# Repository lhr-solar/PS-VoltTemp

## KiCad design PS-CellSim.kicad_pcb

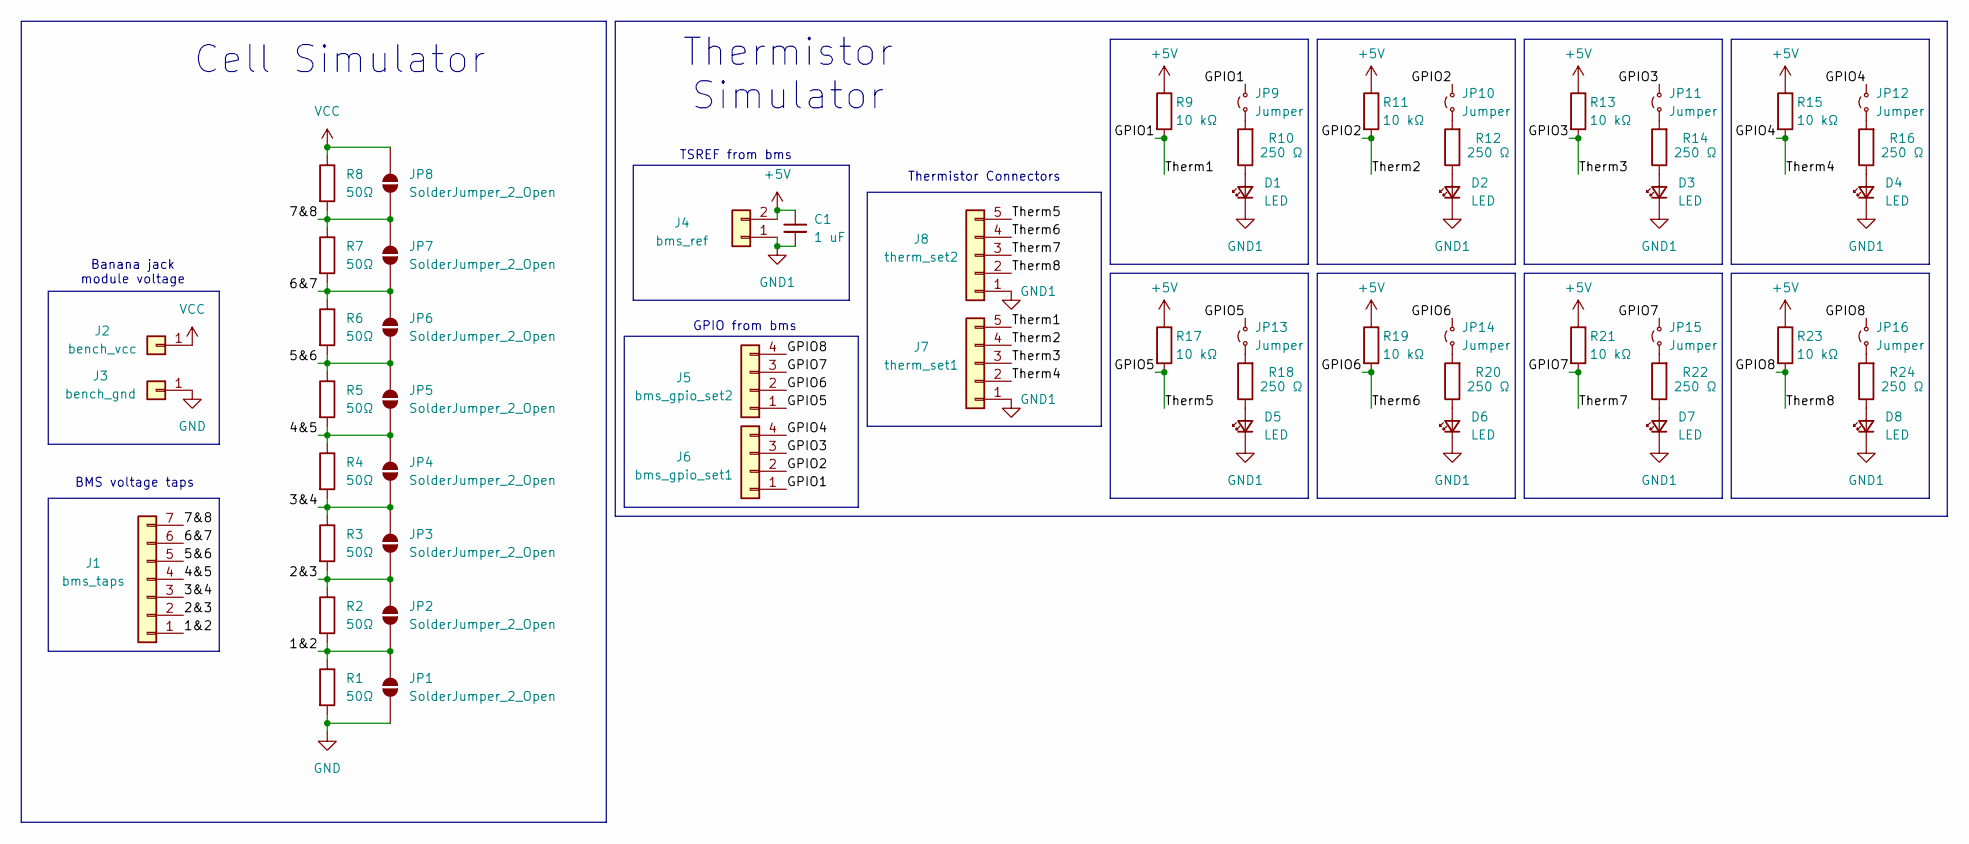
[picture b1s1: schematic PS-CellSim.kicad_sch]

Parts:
C1: 1 uF; C_0603_1608Metric
D1, D2, D3, D4, D5, D6, D7, D8: LED; LED_0603_1608Metric
J1: bms_taps; Molex_Nano-Fit_105313-xx07_1x07_P2.50mm_Horizontal
J2: bench_vcc; Banana_Jack_1_Pin_4mm
J3: bench_gnd; Banana_Jack_1_Pin_4mm
J4: bms_ref; Molex_Nano-Fit_105313-xx02_1x02_P2.50mm_Horizontal
J5: bms_gpio_set2; Molex_Nano-Fit_105313-xx04_1x04_P2.50mm_Horizontal
J6: bms_gpio_set1; Molex_Nano-Fit_105313-xx04_1x04_P2.50mm_Horizontal
J7: therm_set1; Molex_Nano-Fit_105313-xx05_1x05_P2.50mm_Horizontal
J8: therm_set2; Molex_Nano-Fit_105313-xx05_1x05_P2.50mm_Horizontal
JP1, JP2, JP3, JP4, JP5, JP6, JP7, JP8: SolderJumper_2_Open; SolderJumper-2_P1.3mm_Open_TrianglePad1.0x1.5mm
JP9, JP10, JP11, JP12, JP13, JP14, JP15, JP16: Jumper; PinHeader_1x02_P2.00mm_Vertical
R1, R2, R3, R4, R5, R6, R7, R8: 50Ω; R_0603_1608Metric
R9, R11, R13, R15, R17, R19, R21, R23: 10 kΩ; R_0603_1608Metric
R10, R12, R14, R16, R18, R20, R22, R24: 250 Ω; R_0603_1608Metric

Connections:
+5V: C1.1, J4.2, R9.1, R11.1, R13.1, R15.1, R17.1, R19.1, R21.1, R23.1
/1&2: J1.1, JP1.2 (B), JP2.1 (A), R1.1, R2.2
/2&3: J1.2, JP2.2 (B), JP3.1 (A), R2.1, R3.2
/3&4: J1.3, JP3.2 (B), JP4.1 (A), R3.1, R4.2
/4&5: J1.4, JP4.2 (B), JP5.1 (A), R4.1, R5.2
/5&6: J1.5, JP5.2 (B), JP6.1 (A), R5.1, R6.2
/6&7: J1.6, JP6.2 (B), JP7.1 (A), R6.1, R7.2
/7&8: J1.7, JP7.2 (B), JP8.1 (A), R7.1, R8.2
/GPIO1: J6.1, J7.5, JP9.2 (B), R9.2
/GPIO2: J6.2, J7.4, JP10.2 (B), R11.2
/GPIO3: J6.3, J7.3, JP11.2 (B), R13.2
/GPIO4: J6.4, J7.2, JP12.2 (B), R15.2
/GPIO5: J5.1, J8.5, JP13.2 (B), R17.2
/GPIO6: J5.2, J8.4, JP14.2 (B), R19.2
/GPIO7: J5.3, J8.3, JP15.2 (B), R21.2
/GPIO8: J5.4, J8.2, JP16.2 (B), R23.2
GND: J3.1 (Pin_1_1), JP1.1 (A), R1.2
GND1: C1.2, D1.1 (K), D2.1 (K), D3.1 (K), D4.1 (K), D5.1 (K), D6.1 (K), D7.1 (K), D8.1 (K), J4.1, J7.1, J8.1
unnamed: D1.2 (A), R10.1
unnamed: D2.2 (A), R12.1
unnamed: D3.2 (A), R14.1
unnamed: D4.2 (A), R16.1
unnamed: D5.2 (A), R18.1
unnamed: D6.2 (A), R20.1
unnamed: D7.2 (A), R22.1
unnamed: D8.2 (A), R24.1
unnamed: JP9.1 (A), R10.2
unnamed: JP10.1 (A), R12.2
unnamed: JP11.1 (A), R14.2
unnamed: JP12.1 (A), R16.2
unnamed: JP13.1 (A), R18.2
unnamed: JP14.1 (A), R20.2
unnamed: JP15.1 (A), R22.2
unnamed: JP16.1 (A), R24.2
VCC: J2.1 (Pin_1_1), JP8.2 (B), R8.1

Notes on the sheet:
Cell Simulator
BMS voltage taps
Banana jack module voltage
TSREF from bms
Thermistor Connectors
GPIO from bms
Thermistor Simulator

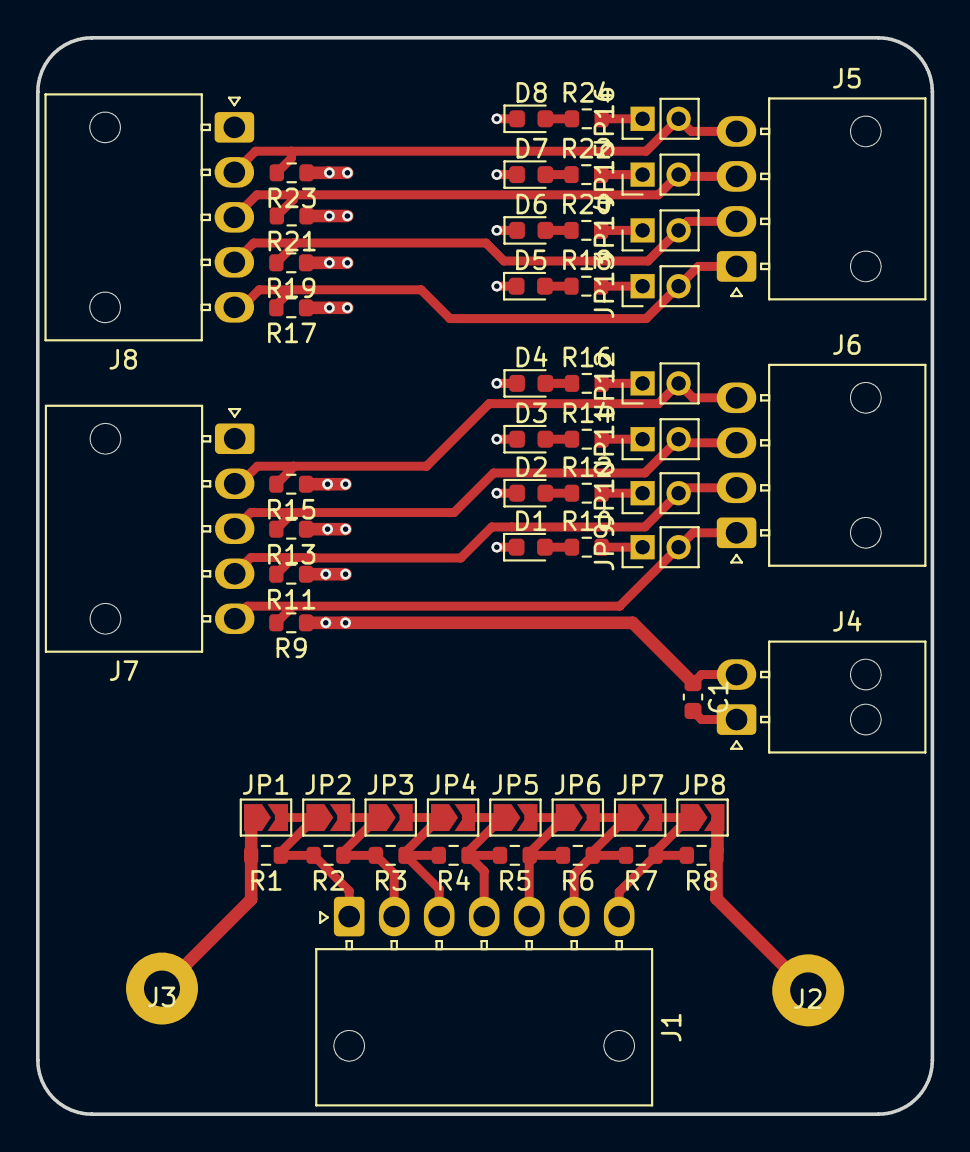
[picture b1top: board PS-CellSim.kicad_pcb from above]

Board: 2 copper layers, 49.7 x 59.8 mm, 57 parts (0 on the bottom side), 35 nets.

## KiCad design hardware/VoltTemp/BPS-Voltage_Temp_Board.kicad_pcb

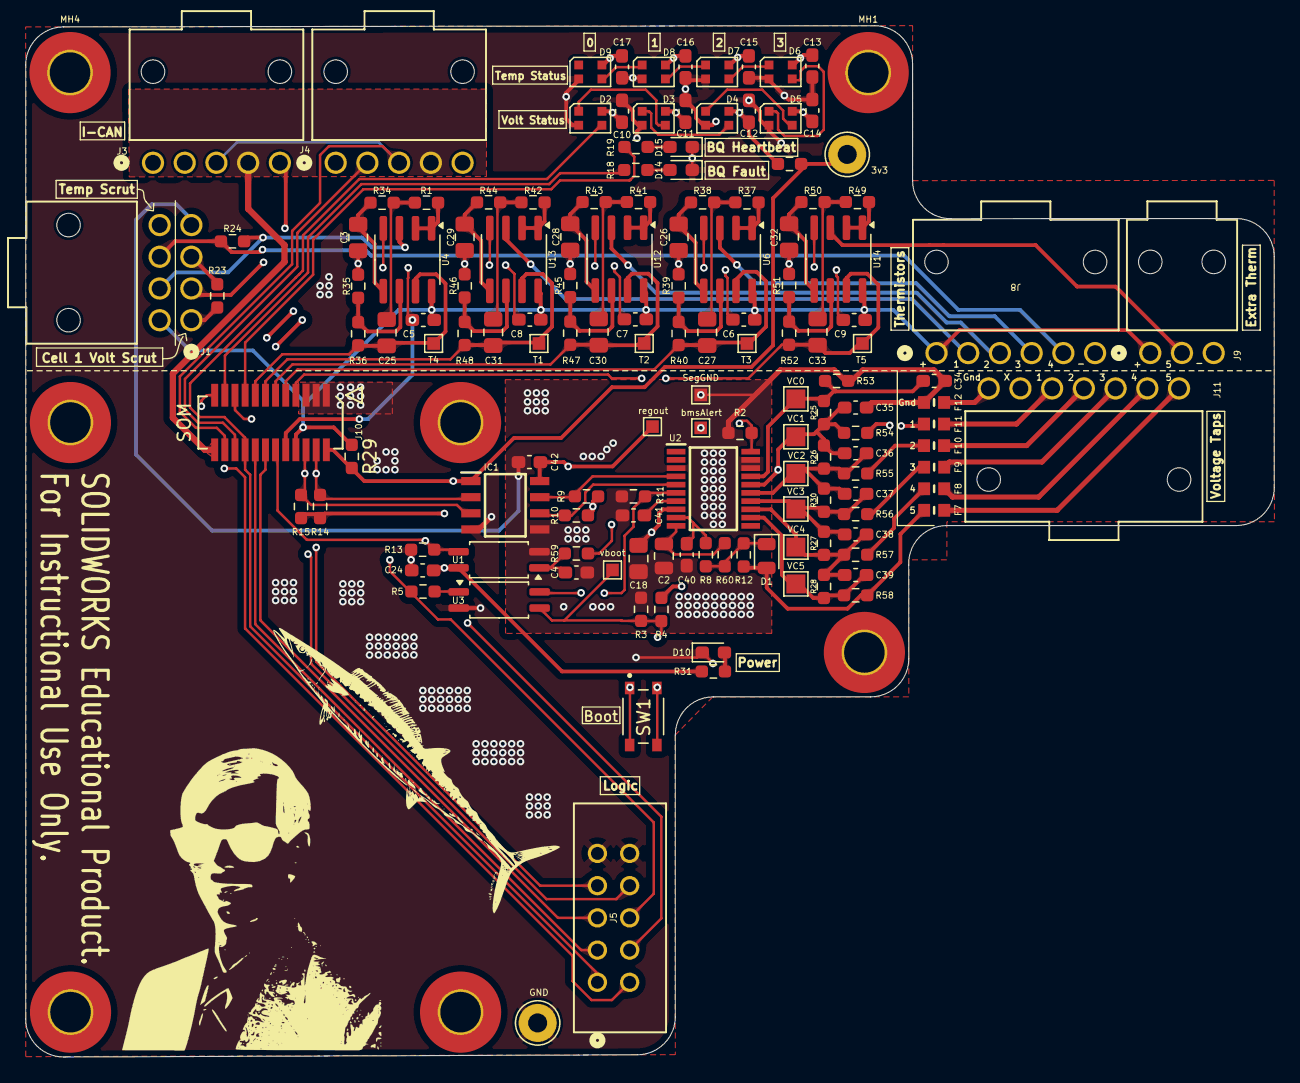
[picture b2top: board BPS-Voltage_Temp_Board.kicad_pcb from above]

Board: 4 copper layers, 98.4 x 81.3 mm, 146 parts (0 on the bottom side), 91 nets.

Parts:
C2: 10μF; C_0805_2012Metric
C3, C26, C28, C29, C32: 1uF; C_0805_2012Metric_Pad1.18x1.45mm_HandSolder
C4: 470pF; C_0603_1608Metric_Pad1.08x0.95mm_HandSolder
C5, C6, C7, C8, C9, C24, C42: 0.1uF; C_0603_1608Metric_Pad1.08x0.95mm_HandSolder
C10, C11, C12, C13, C14, C15, C16, C17: 100nF; C_0603_1608Metric_Pad1.08x0.95mm_HandSolder
C18: 4.7uF; C_0805_2012Metric_Pad1.18x1.45mm_HandSolder
C25, C27, C30, C31, C33: 1.2uF; C_0805_2012Metric_Pad1.18x1.45mm_HandSolder
C34, C35, C36, C37, C38, C39, C40, C41: 1uF; C_0603_1608Metric_Pad1.08x0.95mm_HandSolder
D1: D_Zener_Small; D_0805_2012Metric
D2, D3, D4, D5, D6, D7, D8, D9: WS2812B-2020; LED_WS2812B-2020_PLCC4_2.0x2.0mm
D10: 3v3; LED_0603_1608Metric_Pad1.05x0.95mm_HandSolder
D14: BQ-Fault; LED_0603_1608Metric_Pad1.05x0.95mm_HandSolder
D15: BQ_HB; LED_0603_1608Metric_Pad1.05x0.95mm_HandSolder
F7, F8, F9, F10, F11: 10mA; ptc_fuse_FUSC1607X75N
F12: 40mA; ptc_fuse_FUSC1607X75N
IC1: ISO1641BDR
J1: ScrutineeringConn; nanofit_02x04
J3, J4: Conn_01x05; nanofit_01x05
J5: Logic_Analyzer; CONN_SFH11-xxxC-D05-ST-XX_SUL
J8: Conn_01x06; 1053131106
J9: Conn_01x03; 1053131103
J10: 53307-2471; PeripheralSOM
J11: Conn_01x07; 1053131107
LOGO1: Dr. Hallock; Hallock_Image_Small
LOGO2: LHRs; LHRs_LOGO
MH1, MH3, MH4: MountingHole_Pad; MountingHole_3.2mm_M3_Pad_TopBottom
R1, R37, R41, R42, R49: 8.2kΩ; R_0603_1608Metric_Pad0.98x0.95mm_HandSolder
R2: 510kΩ; R_0603_1608Metric_Pad0.98x0.95mm_HandSolder
R3, R5: 2kΩ; R_0603_1608Metric_Pad0.98x0.95mm_HandSolder
R4, R9, R10, R11, R13, R14, R15: 10kΩ; R_0603_1608Metric_Pad0.98x0.95mm_HandSolder
R6, R23, R24, R25, R26, R27, R28, R29, R30: 0Ω; R_0603_1608Metric_Pad0.98x0.95mm_HandSolder
R8, R12: 1kΩ; R_0603_1608Metric_Pad0.98x0.95mm_HandSolder
R18, R19: 120; R_0603_1608Metric_Pad0.98x0.95mm_HandSolder
R31: 4.3k; R_0603_1608Metric_Pad0.98x0.95mm_HandSolder
R34, R38, R43, R44, R50: 27kΩ; R_0603_1608Metric_Pad0.98x0.95mm_HandSolder
R35, R36, R39, R40, R45, R46, R47, R48, R51, R52: 2.7kΩ; R_0603_1608Metric_Pad0.98x0.95mm_HandSolder
R53, R54, R55, R56, R57, R58, R59, R60: 100Ω; R_0603_1608Metric_Pad0.98x0.95mm_HandSolder
SW1: BOOT; SW_TL3365AF180QG
TP1: Regout; TestPoint_Pad_1.0x1.0mm
TP2, TP5: TestPoint; TestPoint_THTPad_D3.0mm_Drill1.5mm
TP3: bmsAlert; TestPoint_Pad_1.0x1.0mm
TP4: SegGND; TestPoint_Pad_1.0x1.0mm
TP6: VBoot; TestPoint_Pad_1.0x1.0mm
TP11, TP12, TP13, TP14, TP15: TP_TempOut; TestPoint_Pad_1.0x1.0mm
U1, U3: EL3H7
U2: BQ7692003PW
U4, U6, U12, U13, U14: TLV9062xD; SOIC-8_3.9x4.9mm_P1.27mm
VC0, VC1, VC2, VC3, VC4, VC5: TestPoint; TestPoint_Pad_1.5x1.5mm

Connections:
+3.3V: C24.1, IC1.1 (VCC1), J10.2 (+3.3v), R6.1, R14.2, R15.2, R29.2, R31.1, TP2.1, U1.4
+24V: J3.4, J4.4, J10.24 (+24V_In)
/BQ_Fault: J10.21 (SPI1_MISO), R18.1
/BQ_HB: J10.17 (SPI1_MOSI), R19.1
/FaultIndicators/ws2812b_pwr: C10.1, C11.1, C12.1, C13.1, C14.1, C15.1, C16.1, C17.1, D2.4 (VDD), D3.4 (VDD), D4.4 (VDD), D5.4 (VDD), D6.4 (VDD), D7.4 (VDD), D8.4 (VDD), D9.4 (VDD), R6.2
/I-CAN_H: J3.3, J4.3, J10.22 (CAN_H)
/I-CAN_L: J3.2, J4.2, J10.20 (CAN_L)
/LedDin: D2.3 (DIN), J5.1 (CH0), J10.18 (SPI2_SCK)
/PB3: J5.2 (CH1), J10.23 (SPI1_SCK)
/PB14: J5.5 (CH4), J10.14 (SPI2_MISO)
/PB15: J5.3 (CH2), J10.16 (SPI2_MOSI)
/ScrutineeringConn/1&2COM: F11.2, J1.3, R23.1
/ScrutineeringConn/1&2COM_OUT: J1.1, R23.2, R54.2
/ScrutineeringConn/rawTemperature4_Pre: J1.7, J8.5, R24.1
/ShieldGND: J1.2, J3.5, J4.5
/TemperatureConn/rawTemperature1: J8.2, U13.3 (+)
/TemperatureConn/rawTemperature2: J8.3, U12.3 (+)
/TemperatureConn/rawTemperature3: J8.4, U6.3 (+)
/TemperatureConn/rawTemperature4: J1.6, R24.2, U4.3 (+)
/TemperatureConn/rawTemperature5: J9.2, U14.3 (+)
/TemperatureFilters/Temperature1: C31.2, J10.13 (ADC1_IN10), R48.2, TP14.1, U13.7
/TemperatureFilters/Temperature2: C30.2, J10.11 (ADC1_IN9), R47.2, TP13.1, U12.7
/TemperatureFilters/Temperature3: C27.2, J10.9 (ADC1_IN7), R40.2, TP12.1, U6.7
/TemperatureFilters/Temperature4: C25.2, J10.15 (ADC1_IN11), R36.2, TP11.1, U4.7
/TemperatureFilters/Temperature5: C33.2, J10.7 (OPAMP1_VINP), R52.2, TP15.1, U14.7
/VoltageConn/1&2COM_ext: F11.1, J11.5
/VoltageConn/2&3COM: F10.2, R55.2
/VoltageConn/2&3COM_ext: F10.1, J11.4
/VoltageConn/3&4COM: F9.2, R56.2
/VoltageConn/3&4COM_ext: F9.1, J11.3
/VoltageConn/4&5COM: F8.2, R57.2
/VoltageConn/4&5COM_ext: F8.1, J11.2
/VoltageConn/VC0: C34.2, R25.2, R53.1, U2.17 (VC0), VC0.1
/VoltageConn/VC1: C35.1, C36.2, R4.1, R25.1, R26.2, R54.1, U2.16 (VC1), VC1.1
/VoltageConn/VC2: C36.1, C37.2, R26.1, R30.2, R55.1, U2.15 (VC2), VC2.1
/VoltageConn/VC3: C37.1, C38.2, R27.2, R30.1, R56.1, U2.14 (VC3), VC3.1
/VoltageConn/VC4: C38.1, C39.2, R27.1, R28.2, R57.1, U2.13 (VC4), VC4.1
/VoltageConn/VC5: C39.1, R28.1, R58.1, U2.12 (VC5), VC5.1
/VoltageConn/last_cell: D1.2 (A), F7.2, R12.2, R58.2
/VoltageConn/last_cell_ext: F7.1, J11.1
/VoltageSense/ALERT: R2.1, R59.2, TP3.1, U2.20 (ALERT)
/VoltageSense/BAT: C2.2, R60.2, U2.10 (BAT)
/VoltageSense/I2C_SCL: IC1.3 (SCL1), J5.8 (CH7), J10.6 (I2C1_SCL), R15.1
/VoltageSense/I2C_SDA: IC1.2 (SDA1), J5.7 (CH6), J10.4 (I2C1_SDA), R14.1
/VoltageSense/V_Boot: R3.1, R4.2, SW1.2, TP6.1, U3.3
/VoltageSense/bmSCL: IC1.6 (SCL2), R10.1, U2.5 (SCL)
/VoltageSense/bmSDA: IC1.7 (SDA2), R9.1, U2.4 (SDA)
/VoltageSense/bmsBoot: R11.2, SW1.1, U2.6 (TS1), U3.4
/VoltageSense/regout: C18.1, C42.1, IC1.8 (VCC2), R9.2, R10.2, TP1.1, U2.8 (REGOUT)
/bmsAlert: J5.4 (CH3), J10.12 (SPI2_NSS), R13.2, U1.3
/bmsEn: J5.6 (CH5), J10.19 (SPI1_NSS), R5.1
GND: C10.2, C11.2, C12.2, C13.2, C14.2, C15.2, C16.2, C17.2, C24.2, D2.2 (VSS), D3.2 (VSS), D4.2 (VSS), D5.2 (VSS), D6.2 (VSS), D7.2 (VSS), D8.2 (VSS), D9.2 (VSS), D10.1 (K), D14.1 (K), D15.1 (K), IC1.4 (GND1), J3.1, J4.1, J5.9 (GND), J5.10 (GND), J10.1 (GND), J10.3 (GND), J10.5 (GND), R13.1, TP5.1, U3.2
GNDA: C3.2, C5.2, C6.2, C7.2, C8.2, C9.2, C26.2, C28.2, C29.2, C32.2, J1.8, J8.6, J9.3, J10.10 (GNDA), R35.1, R39.1, R45.1, R46.1, R51.1, U4.4 (V-), U6.4 (V-), U12.4 (V-), U13.4 (V-), U14.4 (V-)
GND_Seg: C2.1, C4.2, C18.2, C34.1, C35.2, C40.2, C41.2, C42.2, F12.2, IC1.5 (GND2), J1.4, R2.2, R3.2, R11.1, R53.2, TP4.1, U1.2, U2.3 (VSS), U2.18 (SRP), U2.19 (SRN)
unnamed: C4.1, R59.1, U1.1
unnamed: C25.1, R1.2, R34.1
unnamed: C27.1, R37.2, R38.1
unnamed: C30.1, R41.2, R43.1
unnamed: C31.1, R42.2, R44.1
unnamed: C33.1, R49.2, R50.1
unnamed: D1.1 (K), R8.2, R12.1, R60.1
unnamed: D2.1 (DOUT), D3.3 (DIN)
unnamed: D3.1 (DOUT), D4.3 (DIN)
unnamed: D4.1 (DOUT), D5.3 (DIN)
unnamed: D5.1 (DOUT), D6.3 (DIN)
unnamed: D6.1 (DOUT), D7.3 (DIN)
unnamed: D7.1 (DOUT), D8.3 (DIN)
unnamed: D8.1 (DOUT), D9.3 (DIN)
unnamed: D10.2 (A), R31.2
unnamed: D14.2 (A), R18.2
unnamed: D15.2 (A), R19.2
unnamed: F12.1, J11.7
unnamed: R5.2, U3.1
unnamed: C41.1, U2.7 (CAP1)
unnamed: C40.1, R8.1, U2.9 (REGSRC)
unnamed: R1.1, U4.1, U4.2 (-)
unnamed: C3.1, R34.2, U4.5 (+)
unnamed: R35.2, R36.1, U4.6 (-)
unnamed: R37.1, U6.1, U6.2 (-)
unnamed: C26.1, R38.2, U6.5 (+)
unnamed: R39.2, R40.1, U6.6 (-)
unnamed: R41.1, U12.1, U12.2 (-)
unnamed: C28.1, R43.2, U12.5 (+)
unnamed: R45.2, R47.1, U12.6 (-)
unnamed: R42.1, U13.1, U13.2 (-)
unnamed: C29.1, R44.2, U13.5 (+)
unnamed: R46.2, R48.1, U13.6 (-)
unnamed: R49.1, U14.1, U14.2 (-)
unnamed: C32.1, R50.2, U14.5 (+)
unnamed: R51.2, R52.1, U14.6 (-)
VDDA: C5.1, C6.1, C7.1, C8.1, C9.1, J1.5, J8.1, J9.1, J10.8 (VDDA), R29.1, U4.8 (V+), U6.8 (V+), U12.8 (V+), U13.8 (V+), U14.8 (V+)

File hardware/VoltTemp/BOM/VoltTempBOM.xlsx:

Reference | Value | P/N | Footprint | Qty | DNP
D15 | BQ_HB | XL-1608UBC-06A | LED_SMD:LED_0603_1608Metric_Pad1.05x0.95mm_HandSolder | 1
D10 | 3v3 | XL-1608UBC-06A | LED_SMD:LED_0603_1608Metric_Pad1.05x0.95mm_HandSolder | 1
R34,R38,R43,R44,R50 | 27k | TNPU060327K0AYEN00 | Resistor_SMD:R_0603_1608Metric_Pad0.98x0.95mm_HandSolder | 5
U4,U6,U12,U13,U14 | TLV9062xD | TLV9062QDGKRQ1 | Package_SO:SOIC-8_3.9x4.9mm_P1.27mm | 5
SW1 | BOOT | TL3365AF180QG | VoltTemp:SW_TL3365AF180QG | 1
R25,R26,R28,R30 | 0 | SFR03EZPJ000 | Resistor_SMD:R_0603_1608Metric_Pad0.98x0.95mm_HandSolder | 4
R23,R24,R27 | 0 | SFR03EZPJ000 | Resistor_SMD:R_0603_1608Metric_Pad0.98x0.95mm_HandSolder | 3
R35,R36,R39,R40,R45,R46,R47,R48,R51,R52 | 2.7k | SFR03EZPF2701 | Resistor_SMD:R_0603_1608Metric_Pad0.98x0.95mm_HandSolder | 10
J5 | Logic_Analyzer | SFH11-PBPC-D05-ST-BK | UTSVT_Connectors:CONN_SFH11-xxxC-D05-ST-XX_SUL | 1
F7,F8,F9,F10,F11 | 10mA | PTSLR06038V075 | VoltTemp:ptc_fuse_FUSC1607X75N | 5
D14 | BQ-Fault | NCD0603R1 | LED_SMD:LED_0603_1608Metric_Pad1.05x0.95mm_HandSolder | 1
C3,C26,C28,C29,C32,C34,C35,C36,C37,C38,C39,C40,C41 | 1uF | MLASU168SB5105KTNA01 | Capacitor_SMD:C_0603_1608Metric_Pad1.08x0.95mm_HandSolder,Capacitor_SMD:C_0805_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 | 13
C10,C11,C12,C13,C14,C15,C16,C17 | 100nF | MLASH168SB7104KTNA01 | Capacitor_SMD:C_0603_1608Metric_Pad1.08x0.95mm_HandSolder | 8
C5,C6,C7,C8,C9,C24,C42 | 0.1uF | MLASH168SB7104KTNA01 | Capacitor_SMD:C_0603_1608Metric_Pad1.08x0.95mm_HandSolder | 7
IC1 | ISO1641BDR | ISO1641BDR | VoltTemp:ISO1641BDR | 1
C2 | 10uF | GRM21BR61H106KE43K | Capacitor_SMD:C_0805_2012Metric | 1
F12 | 40mA | FUSC1607X75N | VoltTemp:ptc_fuse_FUSC1607X75N | 1
R53,R54,R55,R56,R57,R58,R59,R60 | 100Œ© | ESR03EZPF1000 | Resistor_SMD:R_0603_1608Metric_Pad0.98x0.95mm_HandSolder | 8
R1,R37,R41,R42,R49 | 8.2kŒ© | ERA-3AED822V | Resistor_SMD:R_0603_1608Metric_Pad0.98x0.95mm_HandSolder | 5
U1,U3 | EL3H7 | EL3H7(D)(TA)-VG | UTSVT_ICs:EL3H7 | 2
R31 | 4.3k | CRCW06034K30FKTA | Resistor_SMD:R_0603_1608Metric_Pad0.98x0.95mm_HandSolder | 1
R5 | 2k | CRCW06032K10FKEA | Resistor_SMD:R_0805_2012Metric | 1
R8,R12 | 1k | CRCW06031K00FKEI | Resistor_SMD:R_0603_1608Metric_Pad0.98x0.95mm_HandSolder | 2
R9,R10,R11,R13,R14,R15 | 10k | CRCW060310K0FKEI | Resistor_SMD:R_0603_1608Metric_Pad0.98x0.95mm_HandSolder | 6
R18,R19 | 120 | CRCW0603120RFKEC | Resistor_SMD:R_0603_1608Metric_Pad0.98x0.95mm_HandSolder | 2
R2 | 510k | CPF0603B510KE1 | Resistor_SMD:R_0603_1608Metric_Pad0.98x0.95mm_HandSolder | 1
C25,C27,C30,C31,C33 | 1.2uF | C0805C125K4RACTU | Capacitor_SMD:C_0805_2012Metric_Pad1.18x1.45mm_HandSolder | 5
U2 | BQ7692003PW | BQ7692003PW | VoltTemp:BQ7692003PW | 1
J10 | 53307-2471 | 53307-2471 | UTSVT_Connectors:PeripheralSOM | 1
D1 | D_Zener_Small | 1N448W | Diode_SMD:D_0805_2012Metric | 1
C18 | 4.7uF | 08055D475KAT4A | Capacitor_SMD:C_0805_2012Metric_Pad1.18x1.45mm_HandSolder | 1
C4 | 470pF | 06035C471J4Z2A | Capacitor_SMD:C_0603_1608Metric_Pad1.08x0.95mm_HandSolder | 1
J6,J7,J12,J13 | Conn_01x04 | 1053132104 | VoltTemp:1053132104 | 4
J11 | Conn_01x07 | 1053131107 | VoltTemp:1053131107 | 1
J8 | Conn_01x06 | 1053131106 | VoltTemp:1053131106 | 1
J9 | Conn_01x03 | 1053131103 | VoltTemp:1053131103 | 1
D2,D3,D4,D5,D6,D7,D8,D9 | WS2812B-2020 |  | LED_SMD:LED_WS2812B-2020_PLCC4_2.0x2.0mm | 8

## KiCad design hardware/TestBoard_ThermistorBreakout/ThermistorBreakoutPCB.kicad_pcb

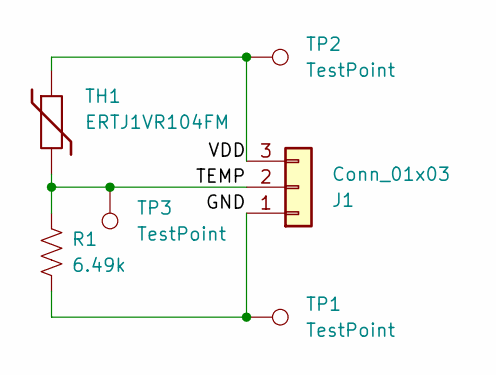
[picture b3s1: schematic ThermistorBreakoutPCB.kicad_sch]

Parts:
J1: Conn_01x03; CONN_SD-105309-100_03_MOL
R1: 6.49k; R_0603_1608Metric_Pad0.98x0.95mm_HandSolder
TH1: ERTJ1VR104FM; R_0603_1608Metric_Pad0.98x0.95mm_HandSolder
TP1, TP2, TP3: TestPoint; TestPoint_Pad_2.0x2.0mm

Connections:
/GND: J1.1, R1.2, TP1.1
/TEMP: J1.2, R1.1, TH1.2, TP3.1
/VDD: J1.3, TH1.1, TP2.1

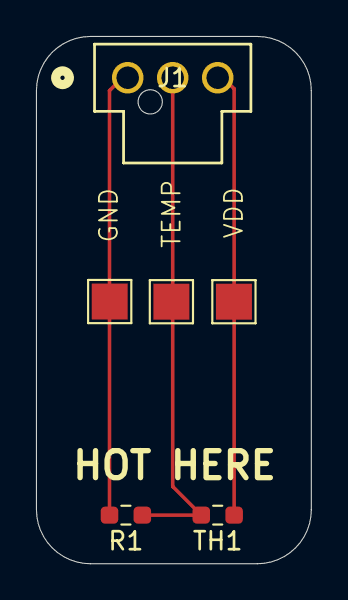
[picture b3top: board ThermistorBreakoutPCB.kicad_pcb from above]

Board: 2 copper layers, 15.3 x 29.3 mm, 6 parts (0 on the bottom side), 3 nets.

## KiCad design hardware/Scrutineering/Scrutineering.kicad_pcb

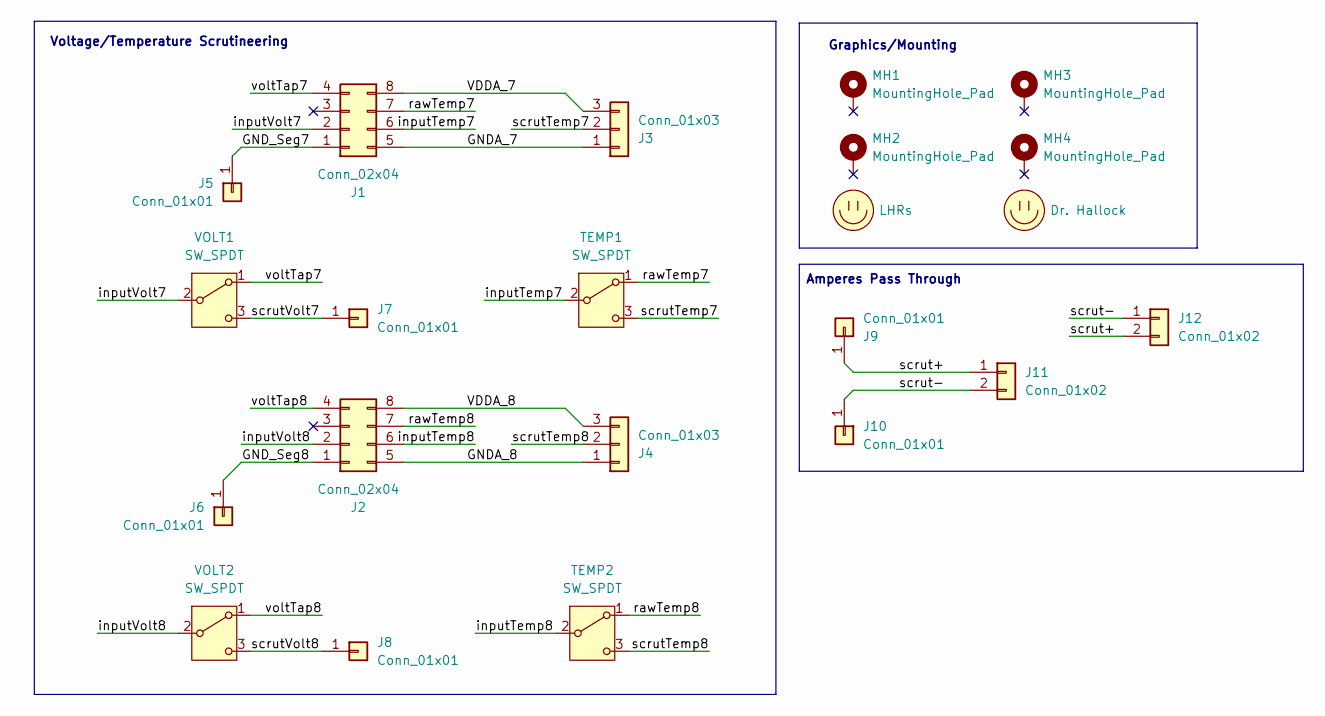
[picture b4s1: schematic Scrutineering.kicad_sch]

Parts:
J1, J2: Conn_02x04; CONN_SD-105310-100_08_MOL
J3, J4: Conn_01x03; CONN_SD-105309-100_03_MOL
J5, J6, J7, J8, J9, J10: Conn_01x01; Banana_Jack_1_Pin_4mm
J11, J12: Conn_01x02; Molex_Nano-Fit_105309-xx02_1x02_P2.50mm_Vertical
LOGO1: Dr. Hallock; Hallock_Image_Small
LOGO2: LHRs; LHRs_LOGO
MH1, MH2, MH3, MH4: MountingHole_Pad; MountingHole_3.2mm_M3_Pad_TopBottom
TEMP1, TEMP2: SW_SPDT; SW_Slide_SPDT_Straight_CK_OS102011MS2Q
VOLT1, VOLT2: SW_SPDT; SW_Slide_SPDT_Straight_CK_OS102011MS2Q

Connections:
/GNDA_7: J1.5, J3.1
/GNDA_8: J2.5, J4.1
/GND_Seg7: J1.1, J5.1
/GND_Seg8: J2.1, J6.1
/VDDA_7: J1.8, J3.3
/VDDA_8: J2.8, J4.3
/inputTemp7: J1.6, TEMP1.2 (B)
/inputTemp8: J2.6, TEMP2.2 (B)
/inputVolt7: J1.2, VOLT1.2 (B)
/inputVolt8: J2.2, VOLT2.2 (B)
/rawTemp7: J1.7, TEMP1.1 (A)
/rawTemp8: J2.7, TEMP2.1 (A)
/scrut+: J9.1, J11.1, J12.2
/scrut-: J10.1, J11.2, J12.1
/scrutTemp7: J3.2, TEMP1.3 (C)
/scrutTemp8: J4.2, TEMP2.3 (C)
/scrutVolt7: J7.1, VOLT1.3 (C)
/scrutVolt8: J8.1, VOLT2.3 (C)
/voltTap7: J1.4, VOLT1.1 (A)
/voltTap8: J2.4, VOLT2.1 (A)

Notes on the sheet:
Amperes Pass Through
Voltage/Temperature Scrutineering
Graphics/Mounting

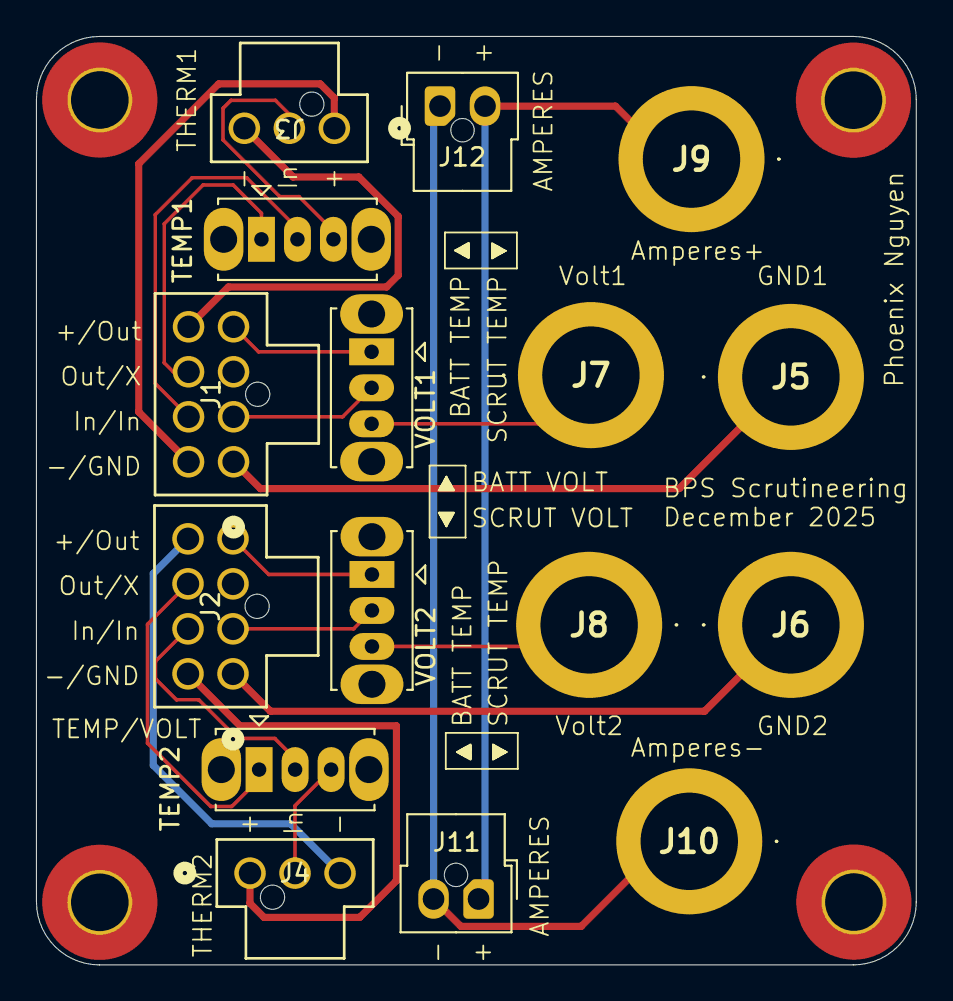
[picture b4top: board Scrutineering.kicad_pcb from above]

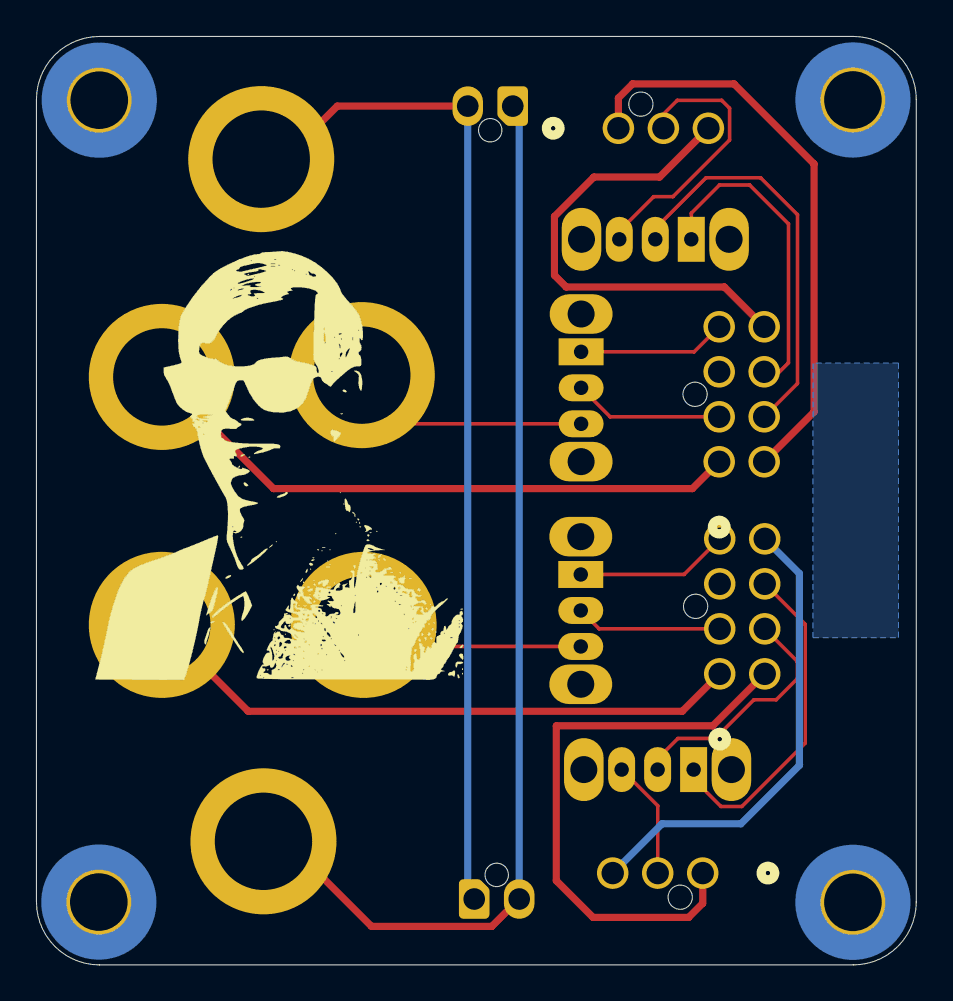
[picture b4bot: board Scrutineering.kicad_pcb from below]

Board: 2 copper layers, 48.9 x 51.6 mm, 22 parts (2 on the bottom side), 20 nets.

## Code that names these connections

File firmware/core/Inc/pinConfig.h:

#pragma once

#include "common.h"
#include "stm32xx_hal.h"

// Pin configuration for LEDs and heartbeat
//================================================================================
#define HEARTBEAT_PORT      GPIOB
#define HEARTBEAT_PIN       GPIO_PIN_11

#define BQ_HEARTBEAT_PORT   GPIOA
#define BQ_HEARTBEAT_PIN    GPIO_PIN_12

#define BQ_FAULT_PORT       GPIOA
#define BQ_FAULT_PIN        GPIO_PIN_11

#define BQ_BOOT_PORT        GPIOB
#define BQ_BOOT_PIN         GPIO_PIN_0

#define PSOM_LED1_PORT      GPIOA
#define PSOM_LED1_PIN       GPIO_PIN_7

#define PSOM_LED2_PORT      GPIOA
#define PSOM_LED2_PIN       GPIO_PIN_8

#define PSOM_LED3_PORT      GPIOA
#define PSOM_LED3_PIN       GPIO_PIN_15
//================================================================================

// Pin configuration for the broken out logic analzyer pins
//================================================================================
#define LOGIC_ANALZYER_CH1_PORT GPIOB
#define LOGIC_ANALZYER_CH1_PIN GPIO_PIN_3

#define LOGIC_ANALZYER_CH2_PORT GPIOB
#define LOGIC_ANALZYER_CH2_PIN GPIO_PIN_15

#define LOGIC_ANALZYER_CH4_PORT GPIOB
#define LOGIC_ANALZYER_CH4_PIN GPIO_PIN_14
//================================================================================



// Pin configuration for BQ I2C
//================================================================================
#define I2C_PORT            GPIOB
#define I2C_SCL_PIN         GPIO_PIN_6
#define I2C_SDA_PIN         GPIO_PIN_7
//================================================================================

// Pin configuration for ADC 
//================================================================================
// Temp 1 = ADC1_IN10 = PA5 
#define TEMP1_PORT            GPIOA
#define TEMP1_PIN             GPIO_PIN_5
// Temp 2 = ADC1_IN9 = PA4
#define TEMP2_PORT            GPIOA
#define TEMP2_PIN             GPIO_PIN_4
// Temp 3 = ADC1_IN7 = PA2
#define TEMP3_PORT            GPIOA
#define TEMP3_PIN             GPIO_PIN_2
// Temp 4 = ADC1_IN11 = PA6
#define TEMP4_PORT            GPIOA
#define TEMP4_PIN             GPIO_PIN_6
// Temp 5 = OPAMP1_VINP / ADC1_IN5 = PA0
#define TEMP5_PORT            GPIOA
#define TEMP5_PIN             GPIO_PIN_0
//================================================================================

// Pin configuration for BQ CAN 
//================================================================================
#define CAN_PORT            GPIOB
#define CAN_RX              GPIO_PIN_8
#define CAN_TX              GPIO_PIN_9
//================================================================================

// USART pins for PSOM
#define USART_PORT GPIOA
#define USART_TX_PIN GPIO_PIN_9
#define USART_RX_PIN GPIO_PIN_10

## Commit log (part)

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2025-10-05 very scuffed i2c code
2025-10-11 firmware :-)
2025-10-12 minor tweaks :-)
2025-10-12 I added comments to some things
2025-10-12 i forgor how to read
2025-10-12 STEP file generated
2025-10-12 board center origin
2025-10-14 changed to vertical connectors
2025-10-14 added footprints/3d models vertical connectors
2025-10-14 fix 1 trace
2025-10-18 ninjafix thanks lakshay :(
2025-10-18 gerbers
2025-10-18 array w/ cell voltages, sys and protect writing, etc.
2025-10-25 updated BOM
2025-10-25 updated BOM again
2025-10-25 Revert "fix 1 trace"
    This reverts commit af0c854c5f9be3b18890f8714f235c97d2fe5d90.
    :#
2025-10-25 .csv
2025-10-25 it works i suppose
2025-10-25 oopsies
2025-10-25 slight oopsies
2025-11-08 workday 11-8-25
2025-12-06 Replaced Lakshay's tiny banana jacks with real ones
2025-12-18 Some tweaks for stm32l4xx support, still needs CubeMX generated I2C init
2025-12-23 some cleanup + fix psom pins
2025-12-24 fix for psom + uart
2026-01-03 fix unrouted
2026-01-03 Staircase (#6)
    * this is the staircase board :(
    * I added the 3d models for the connectors. Need to swap layers around some
    * Traces finished, passes DRC, need to complete silkscreen
    * changes
    * Initial board done. Labels on everything, yay
    * Goofy pictures and names added
2026-01-12 LCSC BOM & Validation square added
2026-01-12 fixed switch label, some silkscreen
2026-01-14 Updated Gerbers
2026-01-14 Updated Thermistor Test Board
2026-01-18 1-17-24 workday, uart stuff not quite working
2026-01-22 added .venv to gitignore
2026-01-24 UART tweaked & folders rearranged, cannor test yet :(
2026-01-27 workday changes, start of thread-safe things
2026-01-27 Small bom with mouser things
2026-01-28 trust
2026-01-28 real firmware
2026-01-29 Rev B PCBA (#11)
2026-02-06 testing procedure added :^)
2026-02-15 Working printf, thread-safe voltage readings
2026-02-19 gemini reviews addressed
2026-02-21 writing should work but it doesnt :(
2026-02-21 Reading and writing both work now :^). Ignoring gemini advice to hold mutex, going with lakshay advice to yolo it
2026-02-21 Working R/W, sys_write wrapper has issues w/ printf?
2026-02-22 files made
2026-02-22 Scrutineering (#7)
    * initial schematic and layout
    * updated layout
    * schematic with graphics/mounting
    * graphics stuff
    * fixed routing
    * BOM and gerber (still need to find jack P/N)
2026-02-28 me when I copy amperes
2026-03-01 printing works :DDDD
2026-03-01 4 real ones
2026-03-03 All concerns addressed EXCEPT adding detailed comments to header file (my laptop is about to die so i am pushing)
2026-03-06 still need to add comments
2026-03-06 comments added to header
2026-03-06 i forgor a comment :^(
2026-03-06 adc hotfix
2026-03-06 bruh momento el bitch
2026-03-06 counts works for all adc, temp conv not correct :(
2026-03-06 LUT no work
2026-03-06 not working lut i havent looked at code chat pleaseeee
2026-03-07 BQ Chip Driver (#12)
    * real firmware
    * testing procedure added :^)
    * Working printf, thread-safe voltage readings
    * gemini reviews addressed
    * writing should work but it doesnt :(
    * Reading and writing both work now :^). Ignoring gemini advice to hold mutex, going with lakshay advice to yolo it
2026-03-07 bump sharepoint
2026-03-07 therm calcs
2026-03-07 LUT files, new generator, header
2026-03-07 cleanup
2026-03-07 rm extraneous file
2026-03-07 error handling type
2026-03-07 use init fn
2026-03-07 CAN testing
2026-03-07 add get all readings
2026-03-07 work
2026-03-07 raw volts
2026-03-07 more pretty
2026-03-07 doc comments
2026-03-07 shut upppp clankerrrr
2026-03-07 Temp Read Firmware (#13)
    * real firmware
    * testing procedure added :^)
    * Working printf, thread-safe voltage readings
    * gemini reviews addressed
    * writing should work but it doesnt :(
    * Reading and writing both work now :^). Ignoring gemini advice to hold mutex, going with lakshay advice to yolo it
2026-03-07 preliminary tasks added
2026-03-08 voltage task is working, CAN task is WIP untested on hardware, step through works
2026-03-08 CAN now outputs something or another, probably wrong
2026-03-12 add .venv to gitignore
2026-03-12 fix?
2026-03-12 only push
2026-03-12 test
2026-03-12 bruh
2026-03-12 uncomment main
2026-03-12 Build tests for all volttemp configs (#15)
    * fix?
    * only push
    * test
    * bruh
2026-03-12 wrote a lot of code, may or may not work
2026-03-13 ts actually cooked, i've tested none of this code lmao
2026-03-13 fix test for build
2026-03-13 fuck you ravi
2026-03-13 main works
2026-03-13 voltage measurements
2026-03-13 little shah
2026-03-13 impement print slcan task
2026-03-13 balls
2026-03-13 add CAN USB mirror macro
2026-03-13 some gemini stuff
2026-03-13 remove extraneous canbus_send
2026-03-13 add better comments for packing messages
2026-03-13 better comments for what the threads do
2026-03-13 completely untested on hw :3
2026-03-13 make better test
2026-03-13 add funny little static assert
2026-03-14 doesn't work :(
2026-03-14 overhaul led driver
2026-03-14 some of ravi's comments
2026-03-14 fuck
2026-03-14 fix build
2026-03-14 BQ Status LEDs (#17)
    * overhaul led driver
    * fuck
    * fix build
2026-03-14 cringe
2026-03-14 stil doesn't work, and i blame changxu
2026-03-14 add a canbus test
2026-03-26 enable auto retransmission
2026-03-30 remove not needed config info + add bq fault led
2026-03-31 add logic analyzer toggles
2026-04-01 fix bq heartbeat error
2026-04-01 fixed some funky bugs that we're not gonna talk about
2026-04-01 don't u worry ur lil head lil shah
2026-04-01 address comments + add more commnts
2026-04-01 move bq init stuff to volt task
2026-04-01 add voltage bounding
2026-04-02 lakshay
2026-04-02 Can Integration (#14)
    * CAN testing
    * preliminary tasks added
    * voltage task is working, CAN task is WIP untested on hardware, step through works
    * CAN now outputs something or another, probably wrong
    * add .venv to gitignore
    * uncomment main
2026-04-04 update voltage thread with correct bq fault msg
2026-04-04 add datasheets folder
2026-04-04 initial testing for balancing (no balancing code in this commit)
2026-04-04 cell balancing automatically finds highest value cell and sets it to balance
2026-04-04 balancing commands file made :^)
2026-04-04 bal works, need to implement RX msg to set which cell
2026-04-11 test task renamed for balancing to work w/ main perchance
2026-04-11 now works when cell 4 needs to be balanced - verified all cells will be balanced if high using scope
2026-04-11 Should be able to receive can now :^)
2026-04-12 Revert "balls"
    This reverts commit f5000a94a85eb75e0500f687026b8b1c65082daf.
2026-04-12 update tempearture can message formatting
2026-04-25 rev c
2026-04-25 jlcpcb assembly files
2026-04-25 reboot bms function has been added
2026-04-25 volttemp gerber stuff
2026-06-15 Rev C (#21)
    * rev c
    * balls
    * balls
    * jlcpcb assembly files
    * volttemp gerber stuff
2026-06-15 Temperature Scrutineering PCB (#22)
    * initial schematic and layout
    * updated layout
    * schematic with graphics/mounting
    * graphics stuff
    * fixed routing
    * BOM and gerber (still need to find jack P/N)
